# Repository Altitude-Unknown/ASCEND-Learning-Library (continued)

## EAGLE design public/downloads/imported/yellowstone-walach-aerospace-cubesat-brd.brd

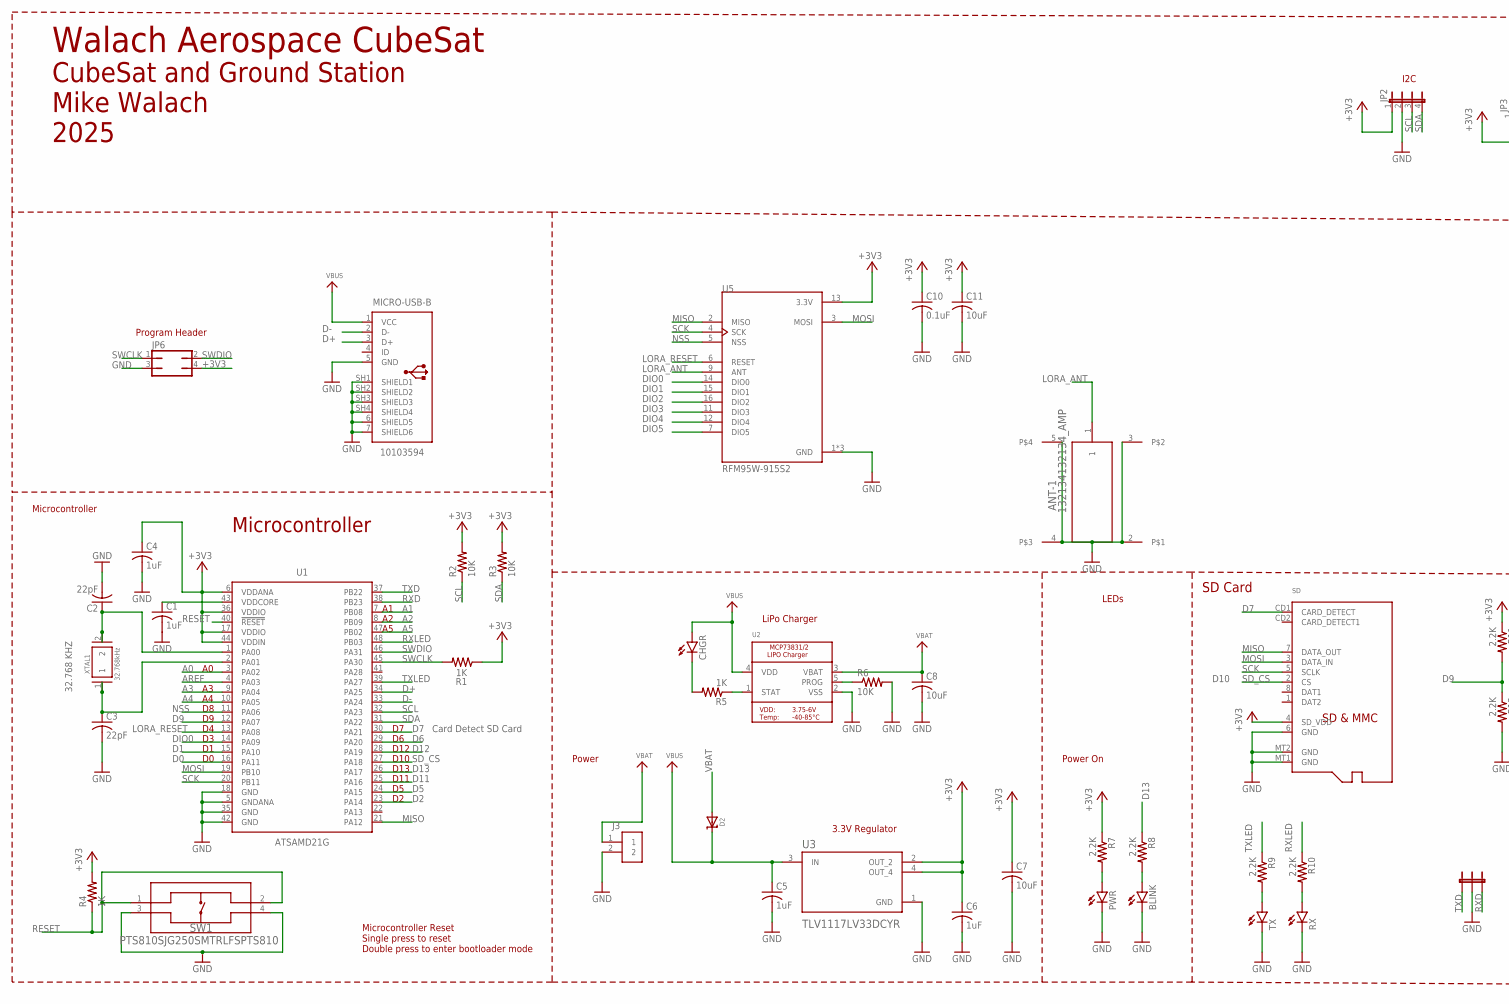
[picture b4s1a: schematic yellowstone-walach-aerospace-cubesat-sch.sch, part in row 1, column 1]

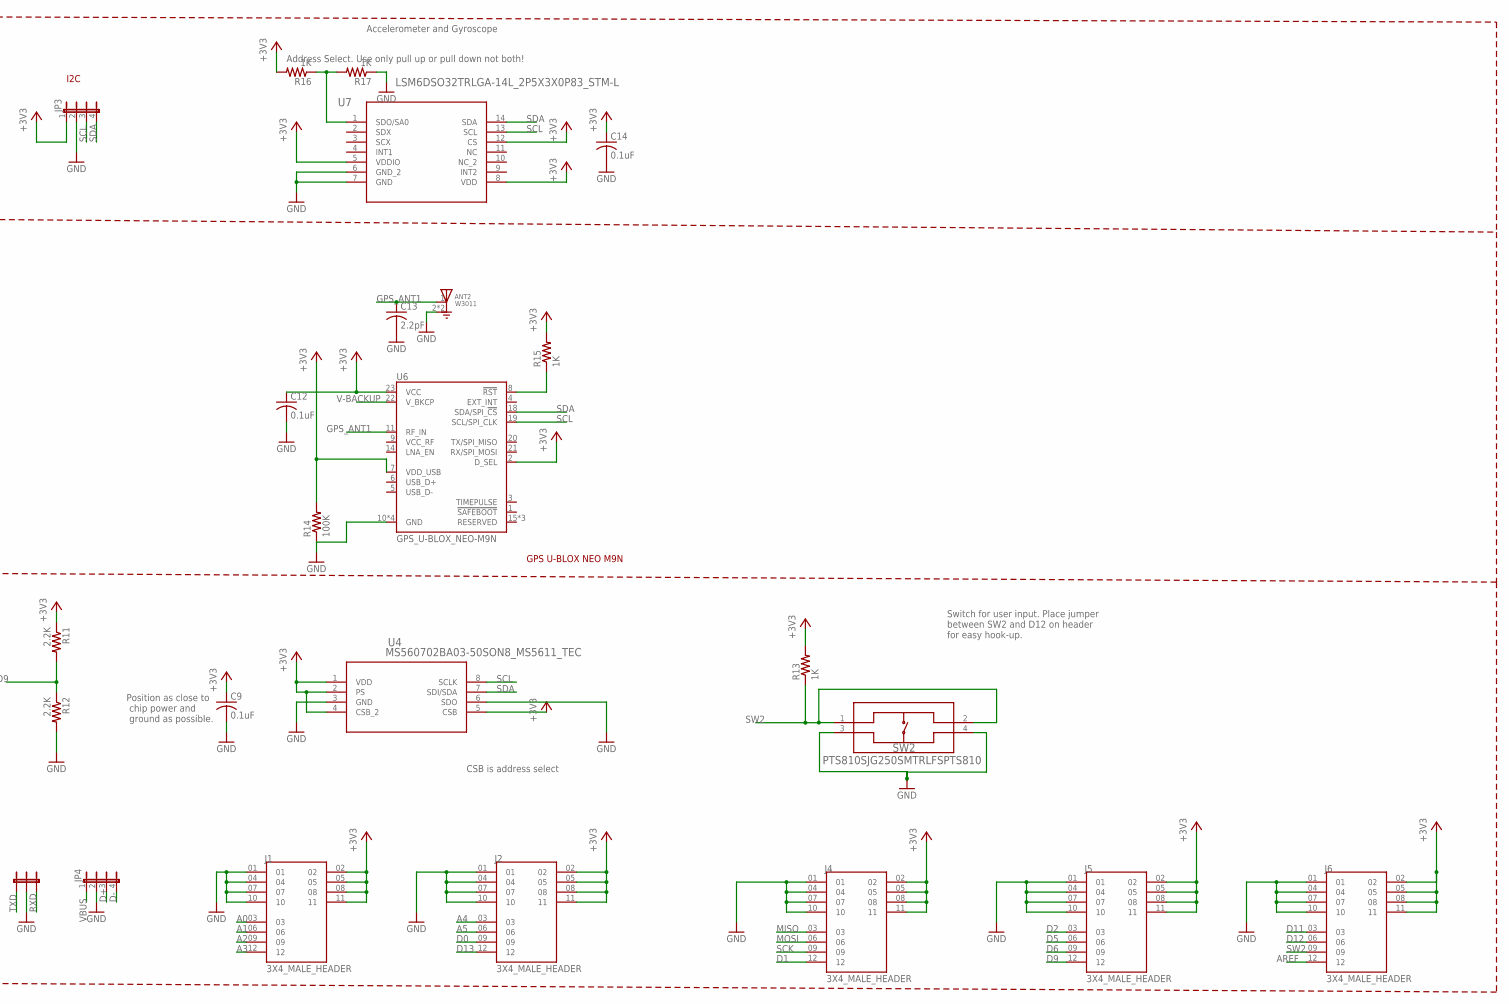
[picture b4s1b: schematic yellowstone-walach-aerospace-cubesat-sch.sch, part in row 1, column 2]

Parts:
ANT2: W3011; XDCR_W3011
ANT-1: 132134132134_AMP; 132134_AMP
BLINK: LEDSML0805; SML0805
C1, C4, C5, C6: 1uF; C0805
C2, C3: 22pF; C0805
C7, C8, C11: 10uF; C0805
C9, C10, C12, C14: 0.1uF; C0805
C13: 2.2pF; C0805
CHGR: LEDSML0805; SML0805
D2: MICROBUILDER_DIODE-SCHOTTKYSOD-123; MICROBUILDER_SOD-123
J1, J2, J4, J5, J6: 3X4_MALE_HEADER; TSW-104-07-F-T_SAMTEC_TSW-104-07-F-T
J3: S2B-PH-K-S(LF)(SN)
JP2, JP3, JP4: JP4E; JP4
JP5: 3-PIN-JUMPER
JP6: JP2Q
MICRO-USB-B: 10103594
PWR: LEDSML0805; SML0805
R1, R4, R5, R13, R15, R16, R17: 1K; R0805
R2, R3, R6: 10K; R0805
R7, R8, R9, R10, R11, R12: 2.2K; R0805
R14: 100K; R0805
RX: LEDSML0805; SML0805
SD: MICROBUILDER_MICROSD
SW1, SW2: PTS810SJG250SMTRLFSPTS810; PTS810
TX: LEDSML0805; SML0805
U1: ATSAMD21G; QFP50P900X900X120-48
U2: MICROBUILDER_MCP73831/2; MICROBUILDER_SOT23-5
U3: TLV1117LV33DCYR; VREG_TLV1117LV33DCYR
U4: MS560702BA03-50SON8_MS5611_TEC; SON8_MS5611_TEC
U5: RFM95W-915S2; XCVR_RFM95W-915S2
U6: GPS_U-BLOX_NEO-M9N; GPS_NEO-M9N
U7: LSM6DSO32TRLGA-14L_2P5X3X0P83_STM-L; LGA-14L_2P5X3X0P83_STM-L
XTAL1: 32.768kHz; XTAL_ABS07-32.768KHZ-T

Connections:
+3V3: C4.1, C6.1, C7.1, C9.1, C10.1, C11.1, C12.1, C14.1, J1.02, J1.05, J1.08, J1.11, J2.02, J2.05, J2.08, J2.11, J4.02, J4.05, J4.08, J4.11, J5.02, J5.05, J5.08, J5.11, J6.02, J6.05, J6.08, J6.11, JP2.1, JP3.1, JP6.4, R1.1, R2.2, R3.2, R4.2, R7.1, R11.1, R13.2, R14.2, R15.2, R16.2, SD.4 (SD_VDD), U1.6 (VDDANA), U1.17 (VDDIO), U1.36 (VDDIO), U1.44 (VDDIN), U3.2 (OUT_2), U3.4 (OUT_4), U4.1 (VDD), U4.2 (PS), U4.4 (CSB_2), U4.5 (CSB), U5.13 (3.3V), U6.2 (D_SEL), U6.7 (VDD_USB), U6.23 (VCC), U7.5 (VDDIO), U7.8 (VDD), U7.12 (CS)
A0: J1.03, U1.3 (PA02)
A1: J1.06, U1.7 (PB08)
A2: J1.09, U1.8 (PB09)
A3: J1.12, U1.9 (PA04)
A4: J2.03, U1.10 (PA05)
A5: J2.06, U1.47 (PB02)
AREF: J6.12, U1.4 (PA03)
D0: J2.09, U1.16 (PA11)
D1: J4.12, U1.15 (PA10)
D2: J5.03, U1.23 (PA14)
D5: J5.06, U1.24 (PA15)
D6: J5.09, U1.29 (PA20)
D7: SD.CD1 (CARD_DETECT), U1.30 (PA21)
D9: J5.12, R11.2, R12.1, U1.12 (PA07)
D11: J6.03, U1.25 (PA16)
D12: J6.06, U1.28 (PA19)
D13: J2.12, R8.1, U1.26 (PA17)
D+: JP4.3, MICRO-USB-B.3 (D+), U1.34 (PA25)
D-: JP4.4, MICRO-USB-B.2 (D-), U1.33 (PA24)
DIO0: U1.14 (PA09), U5.14 (DIO0)
DIO1: U5.15 (DIO1)
DIO2: U5.16 (DIO2)
DIO3: U5.11 (DIO3)
DIO4: U5.12 (DIO4)
DIO5: U5.7 (DIO5)
GND: ANT2.2 (GND), ANT2.3 (GND), ANT-1.2, ANT-1.3, ANT-1.4, ANT-1.5, BLINK.C, C1.2, C2.2, C3.2, C4.2, C5.2, C6.2, C7.2, C8.2, C9.2, C10.2, C11.2, C12.2, C13.2, C14.2, J1.01, J1.04, J1.07, J1.10, J2.01, J2.04, J2.07, J2.10, J3.2, J4.01, J4.04, J4.07, J4.10, J5.01, J5.04, J5.07, J5.10, J6.01, J6.04, J6.07, J6.10, JP2.2, JP3.2, JP4.2, JP5.2, JP6.3, MICRO-USB-B.5 (GND), MICRO-USB-B.6 (SHIELD5), MICRO-USB-B.7 (SHIELD6), MICRO-USB-B.SH1 (SHIELD1), MICRO-USB-B.SH2 (SHIELD2), MICRO-USB-B.SH3 (SHIELD3), MICRO-USB-B.SH4 (SHIELD4), PWR.C, R6.2, R12.2, R14.1, R17.1, RX.C, SD.6 (GND), SD.MT1 (GND), SD.MT2 (GND), SW1.3, SW1.4, SW2.3, SW2.4, TX.C, U1.5 (GNDANA), U1.18 (GND), U1.35 (GND), U1.42 (GND), U2.2 (VSS), U3.1 (GND), U4.3 (GND), U4.6 (SDO), U5.1 (GND), U5.8 (GND), U5.10 (GND), U6.10 (GND), U6.12 (GND), U6.13 (GND), U6.24 (GND), U7.6 (GND_2), U7.7 (GND)
GPS_ANT1: ANT2.1 (FEED), C13.1, U6.11 (RF_IN)
LORA_ANT: ANT-1.1, U5.9 (ANT)
LORA_RESET: U1.13 (PA08), U5.6 (RESET)
MISO: J4.03, SD.7 (DATA_OUT), U1.21 (PA12), U5.2 (MISO)
MOSI: J4.06, SD.3 (DATA_IN), U1.19 (PB10), U5.3 (MOSI)
unnamed: C1.1, U1.43 (VDDCORE)
unnamed: R5.1, U2.1 (STAT)
unnamed: CHGR.C, R5.2
unnamed: R6.1, U2.5 (PROG)
unnamed: BLINK.A, R8.2
unnamed: R9.2, TX.A
unnamed: R10.2, RX.A
unnamed: R15.1, U6.8 (!RST)
unnamed: C3.1, U1.2 (PA01), XTAL1.1
unnamed: R16.1, R17.2, U7.1 (SDO/SA0)
unnamed: C2.1, U1.1 (PA00), XTAL1.2
unnamed: PWR.A, R7.2
NSS: U1.11 (PA06), U5.5 (NSS)
RESET: R4.1, SW1.1, SW1.2, U1.40 (!RESET)
RXD: JP5.3, U1.38 (PB23)
RXLED: R10.1, U1.48 (PB03)
SCK: J4.09, SD.5 (SCLK), U1.20 (PB11), U5.4 (SCK)
SCL: JP2.3, JP3.3, R2.1, U1.32 (PA23), U4.8 (SCLK), U6.19 (SCL/SPI_CLK), U7.13 (SCL)
SDA: JP2.4, JP3.4, R3.1, U1.31 (PA22), U4.7 (SDI/SDA), U6.18 (SDA/SPI_!CS!), U7.14 (SDA)
SD_CS: SD.2 (CS), U1.27 (PA18)
SW2: J6.09, R13.1, SW2.1, SW2.2
SWCLK: JP6.1, R1.2, U1.45 (PA30)
SWDIO: JP6.2, U1.46 (PA31)
TXD: JP5.1, U1.37 (PB22)
TXLED: R9.1, U1.39 (PA27)
V-BACKUP: U6.22 (V_BKCP)
VBAT: C8.1, D2.A, J3.1, U2.3 (VBAT)
VBUS: C5.1, CHGR.A, D2.C, JP4.1, MICRO-USB-B.1 (VCC), U2.4 (VDD), U3.3 (IN)

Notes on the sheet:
Power
SD Card
Microcontroller
32.768 KHZ
CubeSat and Ground Station Mike Walach 2025
LiPo Charger
D10
LEDs
Power On
Microcontroller Reset Single press to reset Double press to enter bootloader mode
Walach Aerospace CubeSat
D13
D11
D12
I2C
Card Detect SD Card
GPS U-BLOX NEO M9N
Address Select. Use only pull up or pull down not both!
Accelerometer and Gyroscope
CSB is address select
Position as close to chip power and ground as possible.
Switch for user input. Place jumper between SW2 and D12 on header for easy hook-up.
Program Header
3.3V Regulator

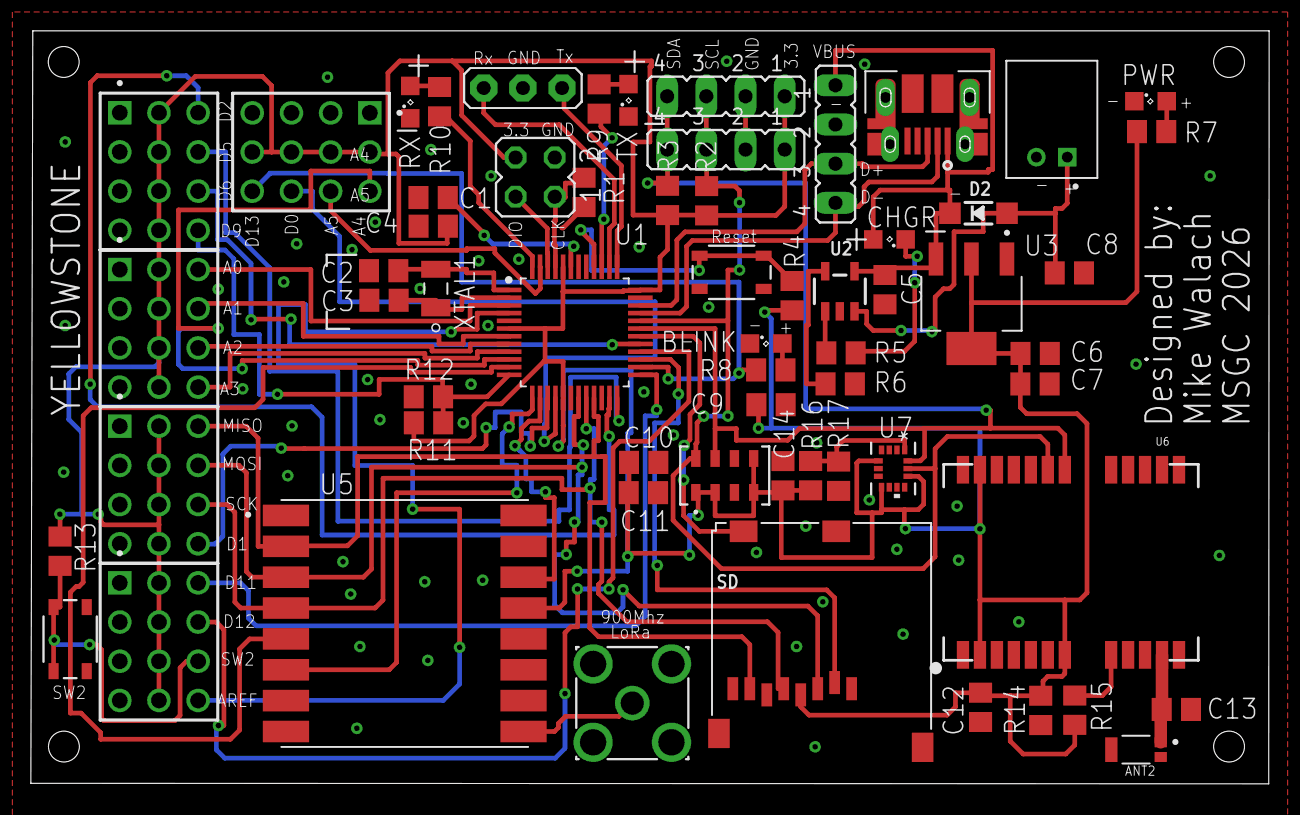
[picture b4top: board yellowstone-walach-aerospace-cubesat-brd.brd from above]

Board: 2 copper layers, 80.3 x 48.8 mm, 62 parts (0 on the bottom side), 54 nets.

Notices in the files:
parts and their libraries:
COPYRIGHT: Copyright (C) 2023 Ultra Librarian. All rights reserved.
COPYRIGHT: Copyright (C) 2025 Ultra Librarian. All rights reserved.
COPYRIGHT: Copyright (C) 2024 Ultra Librarian. All rights reserved.
